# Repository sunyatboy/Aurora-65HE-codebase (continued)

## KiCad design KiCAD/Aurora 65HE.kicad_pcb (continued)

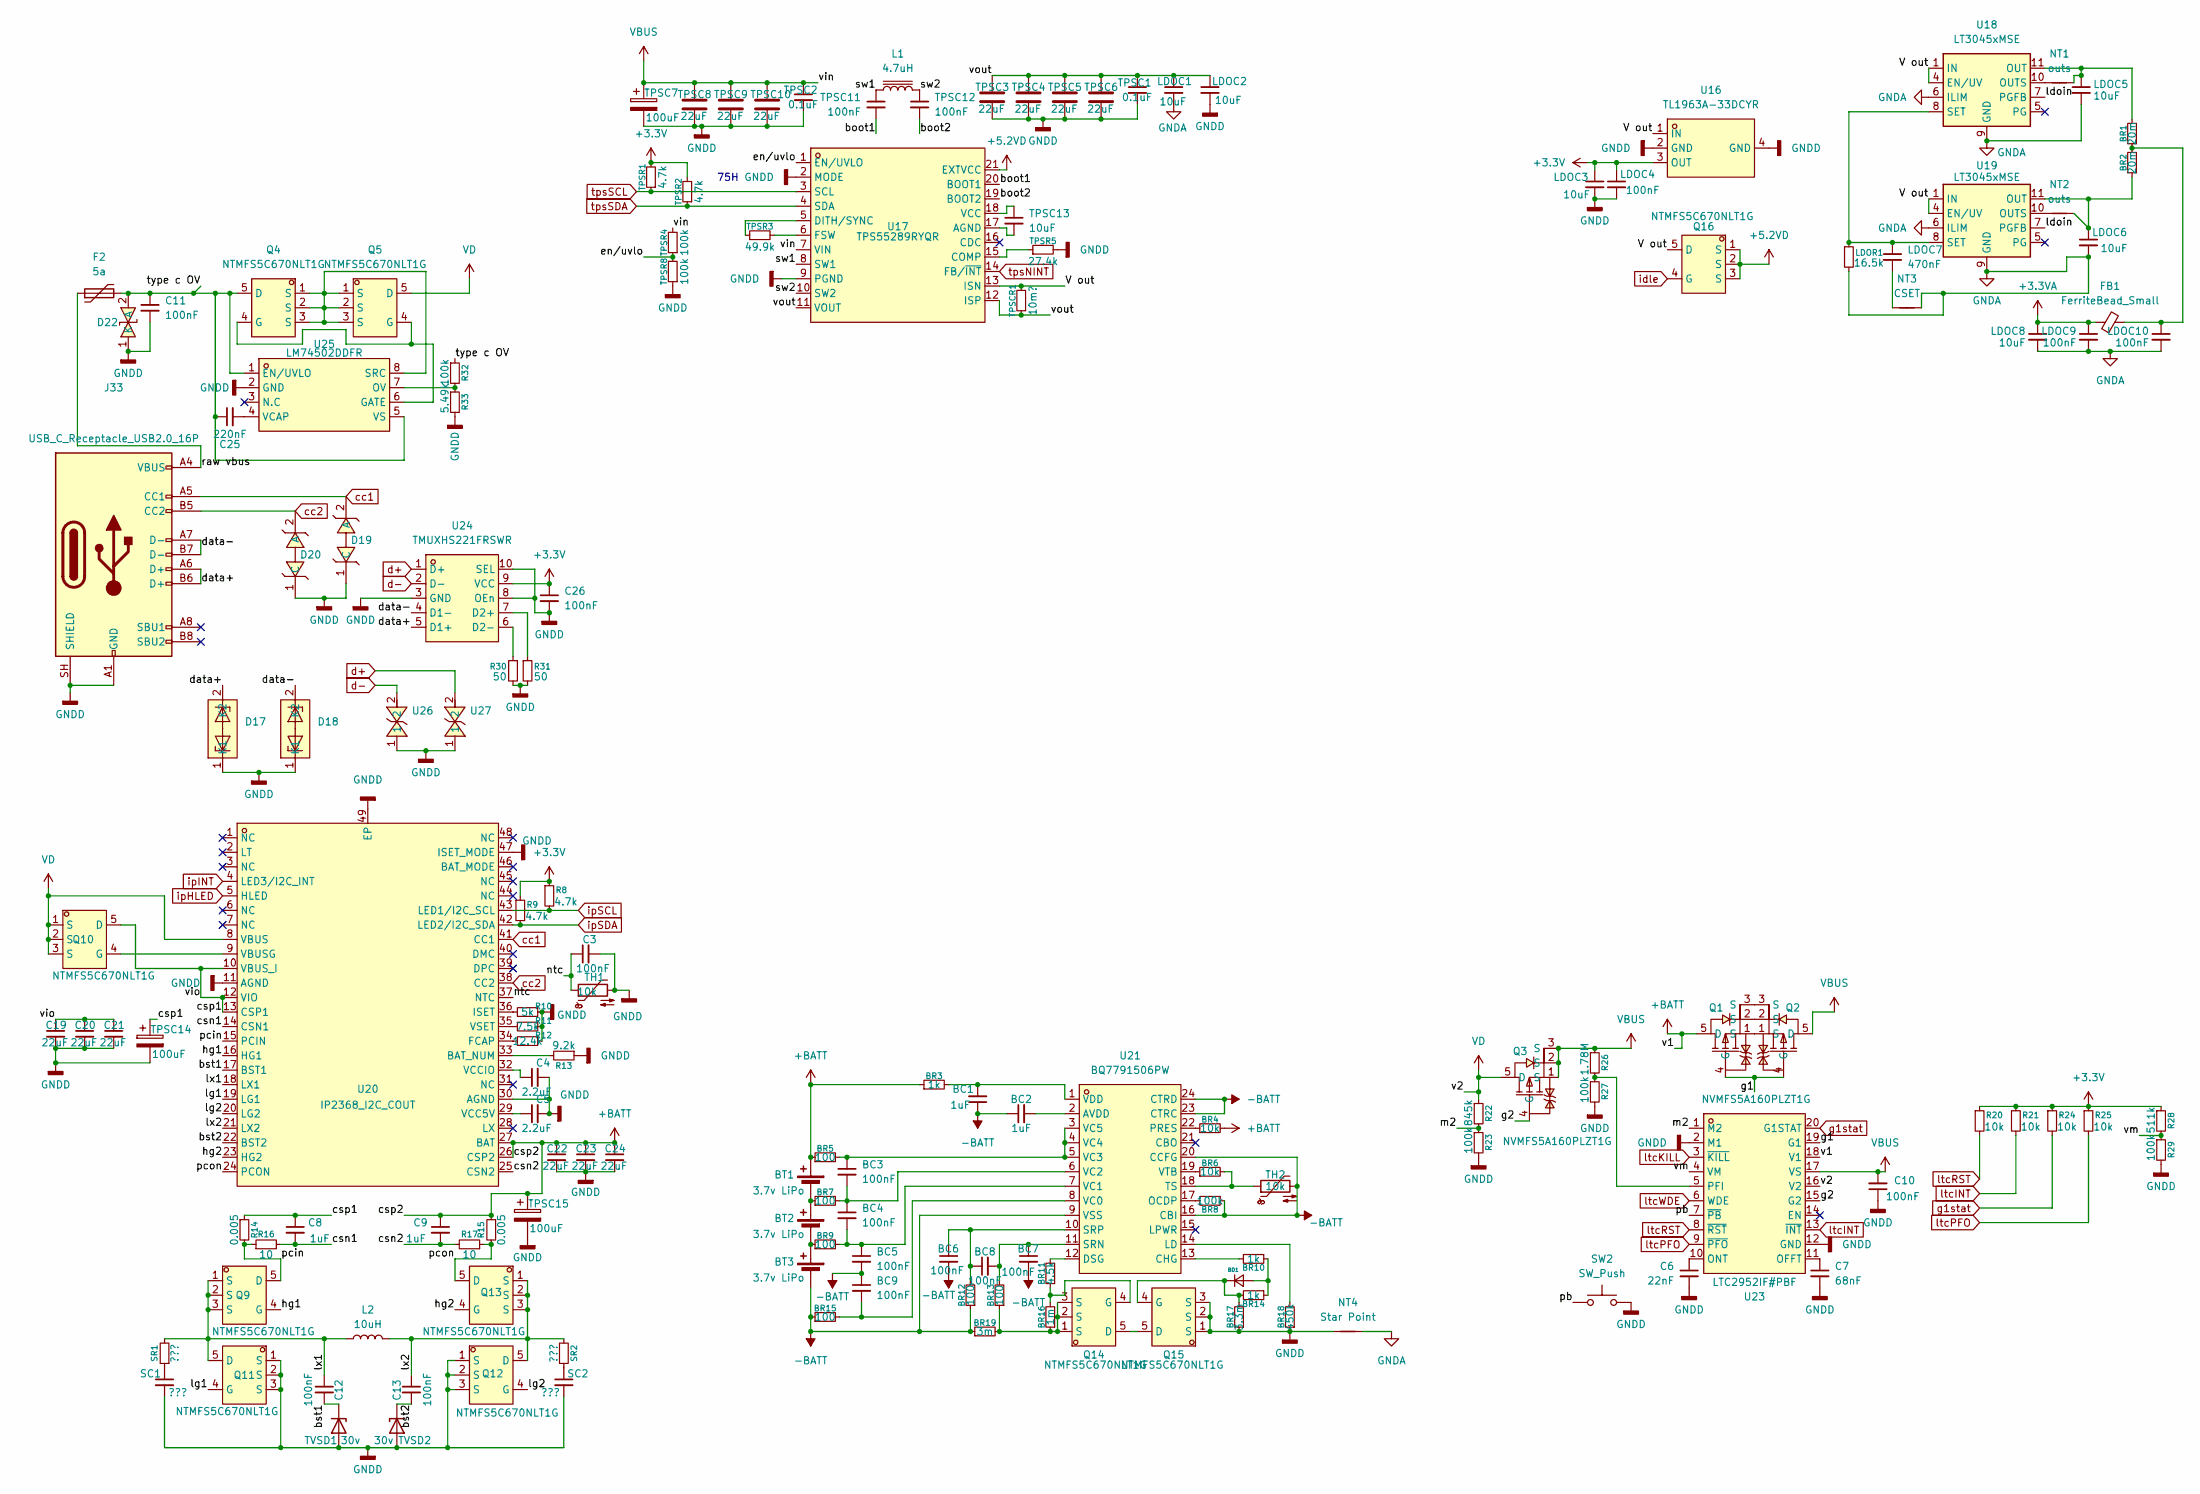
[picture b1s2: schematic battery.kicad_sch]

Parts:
BC1, BC2: 1uF; C_0603_1608Metric
BC3, BC4, BC5, BC6, BC7, BC8, BC9: 100nF; C_0603_1608Metric
BD1: D_0603_1608Metric
BR1, BR2: 20m; R_1206_3216Metric
BR3, BR10, BR14: 1k; R_0603_1608Metric
BR4, BR6: 10k; R_0603_1608Metric
BR5, BR7, BR9, BR12, BR13, BR15: 100; R_0603_1608Metric
BR8: 100k; R_0603_1608Metric
BR11: 4.5k; R_0603_1608Metric
BR16: 1m; R_0603_1608Metric
BR17: 3.3m; R_0603_1608Metric
BR18: 450k; R_0603_1608Metric
BR19: 3m; R_2512_6332Metric
BT1, BT2, BT3: 3.7v LiPo; Battery
C3, C10, C11, C12, C13, C26: 100nF; C_0603_1608Metric
C4, C5: 2.2uF; C_0603_1608Metric
C6: 22nF; C_0603_1608Metric
C7: 68nF; C_0603_1608Metric
C8, C9: 1uF; C_0603_1608Metric
C19, C20, C21, C22, C23, C24: 22uF; C_0603_1608Metric
C25: 220nF; C_0603_1608Metric
D17, D18: PESD24VF1BLYL; DFN1006-2L_L1.0-W0.6-P0.60-BI; MPN PESD24VF1BLYL; LCSC Part C2443373
D19, D20: PESD24VL1BA,115; SOD-323_L1.8-W1.3-LS2.5-BI; MPN PESD24VL1BA,115; LCSC Part C69324
D22: SMBJ24CA_C83268; SMB_L4.6-W3.6-LS5.3-BI; MPN SMBJ24CA; LCSC Part C83268
F2: 5a
FB1: FerriteBead_Small; L_1206_3216Metric
J33: USB_C_Receptacle_USB2.0_16P; USB_C_Receptacle_GCT_USB4105-xx-A_16P_TopMnt_Horizontal
L1: 4.7uH; L_Coilcraft_XAL7070-XXX
L2: 10uH
LDOC1, LDOC2, LDOC3, LDOC5, LDOC6, LDOC8: 10uF; C_1210_3225Metric
LDOC4, LDOC9, LDOC10: 100nF; C_0603_1608Metric
LDOC7: 470nF; C_0603_1608Metric
LDOR1: 16.5k; C_0603_1608Metric
NT1, NT2: outs; NetTie-2_SMD_Pad0.2mm
NT3: CSET; NetTie-2_SMD_Pad0.2mm
NT4: Star Point
Q1, Q2, Q3: NVMFS5A160PLZT1G; DFN-5_L4.9-W5.9-P1.27-LS6.2-BL; MPN NVMFS5A160PLZT1G; LCSC Part C604586
Q4, Q5, Q9, Q10, Q11, Q12, Q13, Q14, Q15, Q16: NTMFS5C670NLT1G; DFN-5_L6.1-W5.1-P1.27-BL; MPN NTMFS5C670NLT1G; LCSC Part C179626
R8, R9: 4.7k; R_0603_1608Metric
R10: 5k; R_0603_1608Metric
R11: 7.5k; R_0603_1608Metric
R12: 12.4k; R_0603_1608Metric
R13: 9.2k; R_0603_1608Metric
R14, R15: 0.005; R_0603_1608Metric
R16, R17: 10; R_0603_1608Metric
R20, R21, R24, R25: 10k; R_0603_1608Metric
R22: 845k; R_0603_1608Metric
R23, R27, R29, R32: 100k; R_0603_1608Metric
R26: 1.78M; R_0603_1608Metric
R28: 511k; R_0603_1608Metric
R30, R31: 50; R_0603_1608Metric
R33: 5.49k; R_0603_1608Metric
SC1, SC2: ???; C_0603_1608Metric
SR1, SR2: ???; R_0603_1608Metric
SW2: SW_Push
TH1, TH2: 10k
TPSC1, TPSC2: 0.1uF; C_0603_1608Metric
TPSC3, TPSC4, TPSC5, TPSC6, TPSC8, TPSC9, TPSC10: 22uF; C_1210_3225Metric
TPSC7, TPSC14, TPSC15: 100uF; C_1210_3225Metric
TPSC11, TPSC12: 100nF; C_0603_1608Metric
TPSC13: 10uF; C_1210_3225Metric
TPSCR1: 10m?; R_2512_6332Metric
TPSR1, TPSR2: 4.7k; C_0603_1608Metric
TPSR3: 49.9k; C_0603_1608Metric
TPSR4, TPSR8: 100k; C_0603_1608Metric
TPSR5: 27.4k; C_0603_1608Metric
TVSD1, TVSD2: 30v
U16: TL1963A-33DCYR; SOT-223_L6.5-W3.5-P2.30-LS7.0-BR; MPN TL1963A-33DCYR; LCSC Part C181262
U17: TPS55289RYQR; VQFN-21_L5.0-W3.0-P0.50-TL; MPN TPS55289RYQR; LCSC Part C5942077
U18, U19: LT3045xMSE; MSOP-12-1EP_3x4.039mm_P0.65mm_EP1.651x2.845mm
U20: IP2368_I2C_COUT; QFN-48_L7.0-W7.0-P0.50-TL-EP5.4-1; MPN IP2368_I2C_COUT; LCSC Part C5372184
U21: BQ7791506PW; TSSOP-24_L7.8-W4.4-P0.65-LS6.4-BR; MPN BQ7791506PW; LCSC Part C2905736
U23: LTC2952IF#PBF; TSSOP-20_L6.5-W4.4-P0.65-LS6.4-BL; MPN LTC2952IF#PBF; LCSC Part C683767
U24: TMUXHS221FRSWR; UQFN-10_L1.8-W1.4-P0.40-TL; MPN TMUXHS221FRSWR; LCSC Part C52989536
U25: LM74502DDFR; SOT-23-8_L2.9-W1.6-P0.65-LS2.8-BL; MPN LM74502DDFR; LCSC Part C3236215
U26, U27: ESD0501BL_C5334572; DFN1006-2L-BI; MPN ESD0501BL; LCSC Part C5334572

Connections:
+3.3V: C26.1, LDOC3.1, LDOC4.1, R8.1, R9.1, R20.1, R21.1, R24.1, R25.1, R28.1, TPSR1.2, TPSR2.2, U16.3 (OUT), U24.9 (VCC); also elsewhere on the board
+3.3VA: FB1.1, LDOC8.1, LDOC9.1; also elsewhere on the board
+5.2VD: Q16.1 (S), Q16.2 (S), Q16.3 (S), U17.21 (EXTVCC); also elsewhere on the board
+BATT: BR3.1, BR4.2, BR5.1, BT1.1 (+), C9.1, C22.1, C23.1, C24.1, Q1.5 (D), R15.1, TPSC15.1, U20.26 (CSP2), U20.27 (BAT), U23.18 (V1)
-BATT: BC1.1, BC2.1, BC5.2, BC6.2, BC7.2, BC9.1, BR8.1, BR12.1, BR15.1, BR19.1, BT3.2 (-), TH2.2, U21.9 (VSS), U21.16 (CBI), U21.20 (CCFG), U21.23 (CTRC), U21.24 (CTRD)
/battery/V out: Q16.5 (D), TPSCR1.2, U16.1 (IN), U17.13 (ISN), U18.1 (IN), U18.2 (IN), U18.3 (IN), U18.4 (EN/UV), U19.1 (IN), U19.2 (IN), U19.3 (IN), U19.4 (EN/UV)
/battery/boot1: TPSC11.2, U17.20 (BOOT1)
/battery/boot2: TPSC12.2, U17.19 (BOOT2)
/battery/bst1: C12.2, TVSD1.1 (K), U20.17 (BST1)
/battery/bst2: C13.2, TVSD2.1 (K), U20.22 (BST2)
/battery/csn1: C8.2, R16.2, U20.14 (CSN1)
/battery/csn2: C9.2, R17.2, U20.25 (CSN2)
/battery/csp1: C8.1, C19.1, C20.1, C21.1, Q10.5 (D), R14.1, TPSC14.1, U20.10 (VBUS_I), U20.12 (VIO), U20.13 (CSP1)
/battery/data+: D17.2 (K2), J33.A6 (D+), J33.B6 (D+), U24.5 (D1+)
/battery/data-: D18.2 (K2), J33.A7 (D-), J33.B7 (D-), U24.4 (D1-)
/battery/en/uvlo: TPSR4.1, TPSR8.2, U17.1 (EN/UVLO)
/battery/g1: Q1.4 (G), Q2.4 (G), U23.19 (G1)
/battery/g2: Q3.4 (G), U23.15 (G2)
/battery/hg1: Q9.4 (G), U20.16 (HG1)
/battery/hg2: Q13.4 (G), U20.23 (HG2)
/battery/ldoin: U18.7 (PGFB), U19.7 (PGFB)
/battery/lg1: Q11.4 (G), U20.19 (LG1)
/battery/lg2: Q12.4 (G), U20.20 (LG2)
/battery/lx1: C12.1, L2.1, Q9.1 (S), Q9.2 (S), Q9.3 (S), Q11.5 (D), SR1.2, U20.18 (LX1)
/battery/lx2: C13.1, L2.2, Q12.5 (D), Q13.1 (S), Q13.2 (S), Q13.3 (S), SR2.2, U20.21 (LX2)
/battery/m2: R22.2, R23.1, U23.1 (M2)
/battery/ntc: C3.1, TH1.1, U20.37 (NTC)
/battery/pb: SW2.1, U23.7 (~PB)
/battery/pcin: Q9.5 (D), R14.2, R16.1, U20.15 (PCIN)
/battery/pcon: Q13.5 (D), R15.2, R17.1, U20.24 (PCON)
/battery/raw vbus: F2.1, J33.A4 (VBUS), J33.A9 (VBUS), J33.B4 (VBUS), J33.B9 (VBUS)
/battery/sw1: L1.1, TPSC11.1, U17.8 (SW1)
/battery/sw2: L1.2, TPSC12.1, U17.10 (SW2)
/battery/type c OV: C11.1, C25.1, D22.2 (A), F2.2, Q4.5 (D), R32.1, U25.1 (EN/UVLO), U25.5 (VS)
/battery/vm: R28.2, R29.1, U23.4 (VM)
/battery/vout: LDOC1.1, LDOC2.1, TPSC1.1, TPSC3.1, TPSC4.1, TPSC5.1, TPSC6.1, TPSCR1.1, U17.11 (VOUT), U17.12 (ISP)
GNDA: LDOC1.2, LDOC5.2, LDOC6.2, LDOC8.2, LDOC9.2, LDOC10.2, LDOR1.2, NT3.2, NT4.2, U18.6 (ILIM), U18.9 (GND), U18.13 (GND), U19.6 (ILIM), U19.9 (GND), U19.13 (GND); also elsewhere on the board
GNDD: BR17.1, BR18.1, C3.2, C4.2, C5.2, C6.2, C7.2, C10.1, C11.2, C19.2, C20.2, C21.2, C22.2, C23.2, C24.2, C26.2, D17.1 (K1), D18.1 (K1), D19.1 (C), D20.1 (C), D22.1 (K), J33.A1 (GND), J33.A12 (GND), J33.B1 (GND), J33.B12 (GND), J33.SH (SHIELD), LDOC2.2, LDOC3.2, LDOC4.2, NT4.1, Q11.1 (S), Q11.2 (S), Q11.3 (S), Q12.1 (S), Q12.2 (S), Q12.3 (S), Q15.1 (S), Q15.2 (S), Q15.3 (S), R10.1, R11.1, R12.1, R13.1, R23.2, R27.2, R29.2, R30.2, R31.2, R33.2, SC1.2, SC2.2, SW2.2, TH1.2, TPSC1.2, TPSC2.2, TPSC3.2, TPSC4.2, TPSC5.2, TPSC6.2, TPSC7.2, TPSC8.2, TPSC9.2, TPSC10.2, TPSC14.2, TPSC15.2, TPSR5.2, TPSR8.1, TVSD1.2 (A), TVSD2.2 (A), U16.2 (GND), U16.4 (GND), U17.2 (MODE), U17.9 (PGND), U20.11 (AGND), U20.30 (AGND), U20.47 (ISET_MODE), U20.49 (EP), U23.2 (M1), U23.12 (GND), U24.3 (GND)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; also elsewhere on the board
unnamed: BD1.2 (A), BR10.1, BR14.1
unnamed: BD1.1 (K), BR14.2, BR17.2, Q15.4 (G)
unnamed: BR1.1, BR2.2, FB1.2, LDOC10.1
unnamed: BR1.2, LDOC5.1, NT1.2, U18.11 (OUT), U18.12 (OUT)
unnamed: BR2.1, LDOC6.1, NT2.2, U19.11 (OUT), U19.12 (OUT)
unnamed: BR13.1, BR16.1, BR19.2, Q14.1 (S), Q14.2 (S), Q14.3 (S)
unnamed: BR7.1, BT1.2 (-), BT2.1 (+)
unnamed: BR9.1, BT2.2 (-), BT3.1 (+)
unnamed: LDOC7.2, NT3.1
unnamed: Q1.1 (S), Q2.1 (S)
unnamed: Q1.2 (S), Q2.2 (S)
unnamed: Q1.3 (S), Q2.3 (S)
unnamed: Q4.4 (G), Q5.4 (G), U25.6 (GATE)
unnamed: Q10.4 (G), U20.9 (VBUSG)
unnamed: Q14.5 (D), Q15.5 (D)
unnamed: BR11.1, BR16.2, Q14.4 (G)
unnamed: SC1.1, SR1.1
unnamed: SC2.1, SR2.1
unnamed: TPSC13.2, U17.17 (AGND)
unnamed: TPSR5.1, U17.15 (COMP)
unnamed: TPSR3.1, U17.5 (DITH/SYNC)
unnamed: TPSR3.2, U17.6 (FSW)
unnamed: TPSC13.1, U17.18 (VCC)
unnamed: NT1.1, U18.10 (OUTS)
unnamed: LDOC7.1, LDOR1.1, U18.8 (SET), U19.8 (SET)
unnamed: NT2.1, U19.10 (OUTS)
unnamed: R13.2, U20.33 (BAT_NUM)
unnamed: R12.2, U20.34 (FCAP)
unnamed: R10.2, U20.36 (ISET)
unnamed: C5.1, U20.29 (VCC5V)
unnamed: C4.1, U20.32 (VCCIO)
unnamed: R11.2, U20.35 (VSET)
unnamed: BC2.2, U21.2 (AVDD)
unnamed: BR10.2, U21.13 (CHG)
unnamed: BR11.2, U21.12 (DSG)
unnamed: BR18.2, U21.14 (LD)
unnamed: BR8.2, U21.17 (OCDP)
unnamed: BR4.1, U21.22 (PRES)
unnamed: BC7.1, BC8.2, BR13.2, U21.11 (SRN)
unnamed: BC6.1, BC8.1, BR12.2, U21.10 (SRP)
unnamed: BR6.2, TH2.1, U21.18 (TS)
unnamed: BC9.2, BR15.2, U21.8 (VC0)
unnamed: BC4.2, BC5.1, BR9.2, U21.7 (VC1)
unnamed: BC3.2, BC4.1, BR7.2, U21.6 (VC2)
unnamed: BC3.1, BR5.2, U21.3 (VC5), U21.4 (VC4), U21.5 (VC3)
unnamed: BC1.2, BR3.2, U21.1 (VDD)
unnamed: BR6.1, U21.19 (VTB)
unnamed: C7.1, U23.11 (OFFT)
unnamed: C6.1, U23.10 (ONT)
unnamed: R26.2, R27.1, U23.5 (PFI)
unnamed: R31.1, U24.7 (D2+)
unnamed: R30.1, U24.6 (D2-)
unnamed: R32.2, R33.1, U25.7 (OV)
unnamed: Q4.1 (S), Q4.2 (S), Q4.3 (S), Q5.1 (S), Q5.2 (S), Q5.3 (S), U25.8 (SRC)
unnamed: C25.2, U25.4 (VCAP)
VBUS: C10.2, Q2.5 (D), Q3.1 (S), Q3.2 (S), Q3.3 (S), R26.1, TPSC2.1, TPSC7.1, TPSC8.1, TPSC9.1, TPSC10.1, TPSR4.2, U17.7 (VIN), U23.17 (VS)
VD: Q3.5 (D), Q5.5 (D), Q10.1 (S), Q10.2 (S), Q10.3 (S), R22.1, U20.8 (VBUS), U23.16 (V2)
cc1: D19.2 (A), J33.A5 (CC1), U20.41 (CC1)
cc2: D20.2 (A), J33.B5 (CC2), U20.38 (CC2)
d+: U24.1 (D+), U27.2; also elsewhere on the board
d-: U24.2 (D-), U26.2; also elsewhere on the board
g1stat: R24.2, U23.20 (G1STAT)
idle: Q16.4 (G)
ipHLED: U20.5 (HLED)
ipINT: U20.4 (LED3/I2C_INT)
ipSCL: R8.2, U20.43 (LED1/I2C_SCL)
ipSDA: R9.2, U20.42 (LED2/I2C_SDA)
ltcINT: R21.2, U23.13 (~INT)
ltcKILL: U23.3 (~KILL)
ltcPFO: R25.2, U23.9 (~PFO)
ltcRST: R20.2, U23.8 (~RST)
ltcWDE: U23.6 (WDE)
tpsNINT: U17.14 (FB/~INT)
tpsSCL: TPSR1.1, U17.3 (SCL)
tpsSDA: TPSR2.1, U17.4 (SDA)

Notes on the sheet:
75H

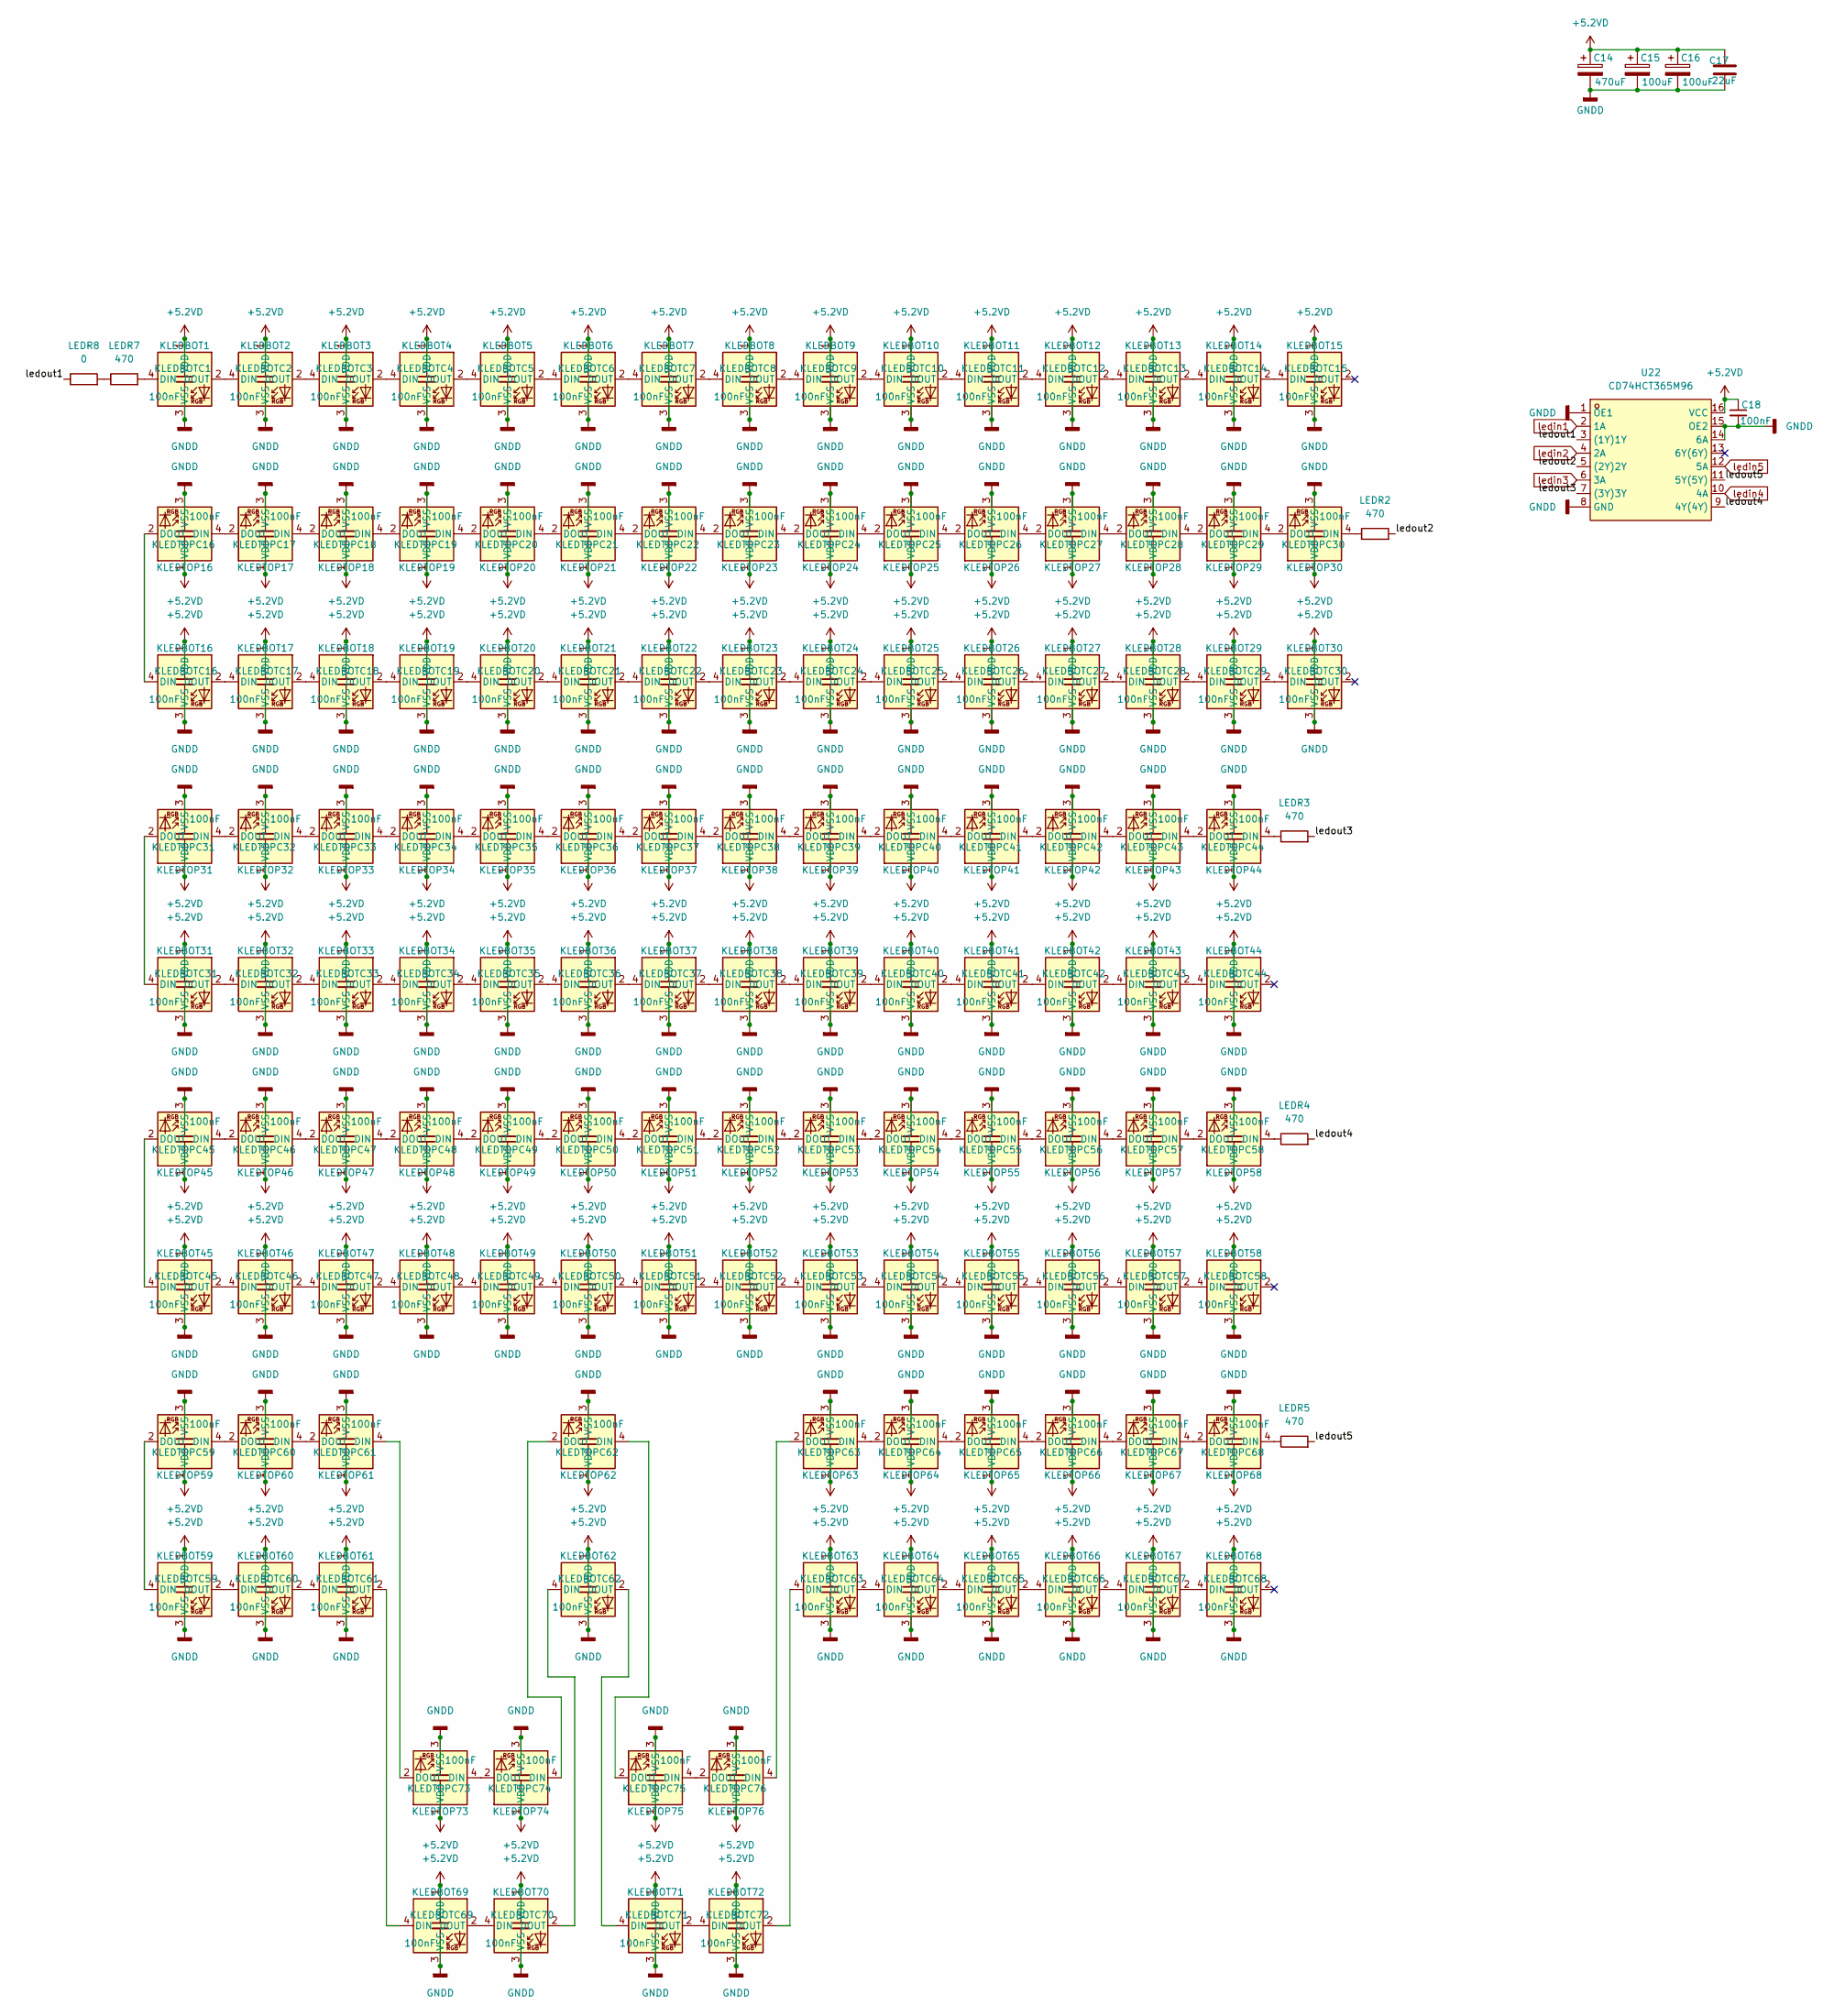
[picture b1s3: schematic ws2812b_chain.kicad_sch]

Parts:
C14: 470uF; C_0603_1608Metric
C15: 100uF; R_1206_3216Metric
C16: 100uF; C_0603_1608Metric
C17: 22uF; C_1210_3225Metric
C18: 100nF; C_0603_1608Metric
KLEDBOT1, KLEDBOT2, KLEDBOT3, KLEDBOT4, KLEDBOT5, KLEDBOT6, KLEDBOT7, KLEDBOT8, KLEDBOT9, KLEDBOT10, KLEDBOT11, KLEDBOT12, KLEDBOT13, KLEDBOT14, KLEDBOT15, KLEDBOT16, KLEDBOT17, KLEDBOT18, KLEDBOT19, KLEDBOT20, KLEDBOT21, KLEDBOT22, KLEDBOT23, KLEDBOT24, KLEDBOT25, KLEDBOT26, KLEDBOT27, KLEDBOT28, KLEDBOT29, KLEDBOT30, KLEDBOT31, KLEDBOT32, KLEDBOT33, KLEDBOT34, KLEDBOT35, KLEDBOT36, KLEDBOT37, KLEDBOT38, KLEDBOT39, KLEDBOT40, KLEDBOT41, KLEDBOT42, KLEDBOT43, KLEDBOT44, KLEDBOT45, KLEDBOT46, KLEDBOT47, KLEDBOT48, KLEDBOT49, KLEDBOT50, KLEDBOT51, KLEDBOT52, KLEDBOT53, KLEDBOT54, KLEDBOT55, KLEDBOT56, KLEDBOT57, KLEDBOT58, KLEDBOT59, KLEDBOT60, KLEDBOT61, KLEDBOT62, KLEDBOT63, KLEDBOT64, KLEDBOT65, KLEDBOT66, KLEDBOT67, KLEDBOT68, KLEDBOT69, KLEDBOT70, KLEDBOT71, KLEDBOT72: WS2812B; LED_WS2812B_PLCC4_5.0x5.0mm_P3.2mm
KLEDBOTC1, KLEDBOTC2, KLEDBOTC3, KLEDBOTC4, KLEDBOTC5, KLEDBOTC6, KLEDBOTC7, KLEDBOTC8, KLEDBOTC9, KLEDBOTC10, KLEDBOTC11, KLEDBOTC12, KLEDBOTC13, KLEDBOTC14, KLEDBOTC15, KLEDBOTC16, KLEDBOTC17, KLEDBOTC18, KLEDBOTC19, KLEDBOTC20, KLEDBOTC21, KLEDBOTC22, KLEDBOTC23, KLEDBOTC24, KLEDBOTC25, KLEDBOTC26, KLEDBOTC27, KLEDBOTC28, KLEDBOTC29, KLEDBOTC30, KLEDBOTC31, KLEDBOTC32, KLEDBOTC33, KLEDBOTC34, KLEDBOTC35, KLEDBOTC36, KLEDBOTC37, KLEDBOTC38, KLEDBOTC39, KLEDBOTC40, KLEDBOTC41, KLEDBOTC42, KLEDBOTC43, KLEDBOTC44, KLEDBOTC45, KLEDBOTC46, KLEDBOTC47, KLEDBOTC48, KLEDBOTC49, KLEDBOTC50, KLEDBOTC51, KLEDBOTC52, KLEDBOTC53, KLEDBOTC54, KLEDBOTC55, KLEDBOTC56, KLEDBOTC57, KLEDBOTC58, KLEDBOTC59, KLEDBOTC60, KLEDBOTC61, KLEDBOTC62, KLEDBOTC63, KLEDBOTC64, KLEDBOTC65, KLEDBOTC66, KLEDBOTC67, KLEDBOTC68, KLEDBOTC69, KLEDBOTC70, KLEDBOTC71, KLEDBOTC72: 100nF; C_0603_1608Metric
KLEDTOP16, KLEDTOP17, KLEDTOP18, KLEDTOP19, KLEDTOP20, KLEDTOP21, KLEDTOP22, KLEDTOP23, KLEDTOP24, KLEDTOP25, KLEDTOP26, KLEDTOP27, KLEDTOP28, KLEDTOP29, KLEDTOP30, KLEDTOP31, KLEDTOP32, KLEDTOP33, KLEDTOP34, KLEDTOP35, KLEDTOP36, KLEDTOP37, KLEDTOP38, KLEDTOP39, KLEDTOP40, KLEDTOP41, KLEDTOP42, KLEDTOP43, KLEDTOP44, KLEDTOP45, KLEDTOP46, KLEDTOP47, KLEDTOP48, KLEDTOP49, KLEDTOP50, KLEDTOP51, KLEDTOP52, KLEDTOP53, KLEDTOP54, KLEDTOP55, KLEDTOP56, KLEDTOP57, KLEDTOP58, KLEDTOP59, KLEDTOP60, KLEDTOP61, KLEDTOP62, KLEDTOP63, KLEDTOP64, KLEDTOP65, KLEDTOP66, KLEDTOP67, KLEDTOP68, KLEDTOP73, KLEDTOP74, KLEDTOP75, KLEDTOP76: WS2812B; LED_WS2812B_PLCC4_5.0x5.0mm_P3.2mm
KLEDTOPC16, KLEDTOPC17, KLEDTOPC18, KLEDTOPC19, KLEDTOPC20, KLEDTOPC21, KLEDTOPC22, KLEDTOPC23, KLEDTOPC24, KLEDTOPC25, KLEDTOPC26, KLEDTOPC27, KLEDTOPC28, KLEDTOPC29, KLEDTOPC30, KLEDTOPC31, KLEDTOPC32, KLEDTOPC33, KLEDTOPC34, KLEDTOPC35, KLEDTOPC36, KLEDTOPC37, KLEDTOPC38, KLEDTOPC39, KLEDTOPC40, KLEDTOPC41, KLEDTOPC42, KLEDTOPC43, KLEDTOPC44, KLEDTOPC45, KLEDTOPC46, KLEDTOPC47, KLEDTOPC48, KLEDTOPC49, KLEDTOPC50, KLEDTOPC51, KLEDTOPC52, KLEDTOPC53, KLEDTOPC54, KLEDTOPC55, KLEDTOPC56, KLEDTOPC57, KLEDTOPC58, KLEDTOPC59, KLEDTOPC60, KLEDTOPC61, KLEDTOPC62, KLEDTOPC63, KLEDTOPC64, KLEDTOPC65, KLEDTOPC66, KLEDTOPC67, KLEDTOPC68, KLEDTOPC73, KLEDTOPC74, KLEDTOPC75, KLEDTOPC76: 100nF; C_0603_1608Metric
LEDR2, LEDR3, LEDR4, LEDR5: 470; LED_2512_6332Metric
LEDR7: 470; C_0603_1608Metric
LEDR8: 0; LED_2512_6332Metric
U22: CD74HCT365M96; SOIC-16_L9.9-W3.9-P1.27-LS6.0-BL-1; MPN CD74HCT365M96; LCSC Part C2676054

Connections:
+5.2VD: C14.1, C15.1, C16.1, C17.1, C18.1, KLEDBOT1.1 (VDD), KLEDBOT2.1 (VDD), KLEDBOT3.1 (VDD), KLEDBOT4.1 (VDD), KLEDBOT5.1 (VDD), KLEDBOT6.1 (VDD), KLEDBOT7.1 (VDD), KLEDBOT8.1 (VDD), KLEDBOT9.1 (VDD), KLEDBOT10.1 (VDD), KLEDBOT11.1 (VDD), KLEDBOT12.1 (VDD), KLEDBOT13.1 (VDD), KLEDBOT14.1 (VDD), KLEDBOT15.1 (VDD), KLEDBOT16.1 (VDD), KLEDBOT17.1 (VDD), KLEDBOT18.1 (VDD), KLEDBOT19.1 (VDD), KLEDBOT20.1 (VDD), KLEDBOT21.1 (VDD), KLEDBOT22.1 (VDD), KLEDBOT23.1 (VDD), KLEDBOT24.1 (VDD), KLEDBOT25.1 (VDD), KLEDBOT26.1 (VDD), KLEDBOT27.1 (VDD), KLEDBOT28.1 (VDD), KLEDBOT29.1 (VDD), KLEDBOT30.1 (VDD), KLEDBOT31.1 (VDD), KLEDBOT32.1 (VDD), KLEDBOT33.1 (VDD), KLEDBOT34.1 (VDD), KLEDBOT35.1 (VDD), KLEDBOT36.1 (VDD), KLEDBOT37.1 (VDD), KLEDBOT38.1 (VDD), KLEDBOT39.1 (VDD), KLEDBOT40.1 (VDD), KLEDBOT41.1 (VDD), KLEDBOT42.1 (VDD), KLEDBOT43.1 (VDD), KLEDBOT44.1 (VDD), KLEDBOT45.1 (VDD), KLEDBOT46.1 (VDD), KLEDBOT47.1 (VDD), KLEDBOT48.1 (VDD), KLEDBOT49.1 (VDD), KLEDBOT50.1 (VDD), KLEDBOT51.1 (VDD), KLEDBOT52.1 (VDD), KLEDBOT53.1 (VDD), KLEDBOT54.1 (VDD), KLEDBOT55.1 (VDD), KLEDBOT56.1 (VDD), KLEDBOT57.1 (VDD), KLEDBOT58.1 (VDD), KLEDBOT59.1 (VDD), KLEDBOT60.1 (VDD), KLEDBOT61.1 (VDD), KLEDBOT62.1 (VDD), KLEDBOT63.1 (VDD), KLEDBOT64.1 (VDD), KLEDBOT65.1 (VDD), KLEDBOT66.1 (VDD), KLEDBOT67.1 (VDD), KLEDBOT68.1 (VDD), KLEDBOT69.1 (VDD), KLEDBOT70.1 (VDD), KLEDBOT71.1 (VDD), KLEDBOT72.1 (VDD), KLEDBOTC1.1, KLEDBOTC2.1, KLEDBOTC3.1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; also elsewhere on the board
/Gemini Lighting/ledout1: LEDR8.1, U22.3 ((1Y)1Y)
/Gemini Lighting/ledout2: LEDR2.2, U22.5 ((2Y)2Y)
/Gemini Lighting/ledout3: LEDR3.2, U22.7 ((3Y)3Y)
/Gemini Lighting/ledout4: LEDR4.2, U22.9 (4Y(4Y))
/Gemini Lighting/ledout5: LEDR5.2, U22.11 (5Y(5Y))
GNDD: C14.2, C15.2, C16.2, C17.2, C18.2, KLEDBOT1.3 (VSS), KLEDBOT2.3 (VSS), KLEDBOT3.3 (VSS), KLEDBOT4.3 (VSS), KLEDBOT5.3 (VSS), KLEDBOT6.3 (VSS), KLEDBOT7.3 (VSS), KLEDBOT8.3 (VSS), KLEDBOT9.3 (VSS), KLEDBOT10.3 (VSS), KLEDBOT11.3 (VSS), KLEDBOT12.3 (VSS), KLEDBOT13.3 (VSS), KLEDBOT14.3 (VSS), KLEDBOT15.3 (VSS), KLEDBOT16.3 (VSS), KLEDBOT17.3 (VSS), KLEDBOT18.3 (VSS), KLEDBOT19.3 (VSS), KLEDBOT20.3 (VSS), KLEDBOT21.3 (VSS), KLEDBOT22.3 (VSS), KLEDBOT23.3 (VSS), KLEDBOT24.3 (VSS), KLEDBOT25.3 (VSS), KLEDBOT26.3 (VSS), KLEDBOT27.3 (VSS), KLEDBOT28.3 (VSS), KLEDBOT29.3 (VSS), KLEDBOT30.3 (VSS), KLEDBOT31.3 (VSS), KLEDBOT32.3 (VSS), KLEDBOT33.3 (VSS), KLEDBOT34.3 (VSS), KLEDBOT35.3 (VSS), KLEDBOT36.3 (VSS), KLEDBOT37.3 (VSS), KLEDBOT38.3 (VSS), KLEDBOT39.3 (VSS), KLEDBOT40.3 (VSS), KLEDBOT41.3 (VSS), KLEDBOT42.3 (VSS), KLEDBOT43.3 (VSS), KLEDBOT44.3 (VSS), KLEDBOT45.3 (VSS), KLEDBOT46.3 (VSS), KLEDBOT47.3 (VSS), KLEDBOT48.3 (VSS), KLEDBOT49.3 (VSS), KLEDBOT50.3 (VSS), KLEDBOT51.3 (VSS), KLEDBOT52.3 (VSS), KLEDBOT53.3 (VSS), KLEDBOT54.3 (VSS), KLEDBOT55.3 (VSS), KLEDBOT56.3 (VSS), KLEDBOT57.3 (VSS), KLEDBOT58.3 (VSS), KLEDBOT59.3 (VSS), KLEDBOT60.3 (VSS), KLEDBOT61.3 (VSS), KLEDBOT62.3 (VSS), KLEDBOT63.3 (VSS), KLEDBOT64.3 (VSS), KLEDBOT65.3 (VSS), KLEDBOT66.3 (VSS), KLEDBOT67.3 (VSS), KLEDBOT68.3 (VSS), KLEDBOT69.3 (VSS), KLEDBOT70.3 (VSS), KLEDBOT71.3 (VSS), KLEDBOT72.3 (VSS), KLEDBOTC1.2, KLEDBOTC2.2, KLEDBOTC3.2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; also elsewhere on the board
unnamed: KLEDBOT1.4 (DIN), LEDR7.2
unnamed: KLEDBOT1.2 (DOUT), KLEDBOT2.4 (DIN)
unnamed: KLEDBOT2.2 (DOUT), KLEDBOT3.4 (DIN)
unnamed: KLEDBOT3.2 (DOUT), KLEDBOT4.4 (DIN)
unnamed: KLEDBOT4.2 (DOUT), KLEDBOT5.4 (DIN)
unnamed: KLEDBOT5.2 (DOUT), KLEDBOT6.4 (DIN)
unnamed: KLEDBOT6.2 (DOUT), KLEDBOT7.4 (DIN)
unnamed: KLEDBOT7.2 (DOUT), KLEDBOT8.4 (DIN)
unnamed: KLEDBOT8.2 (DOUT), KLEDBOT9.4 (DIN)
unnamed: KLEDBOT9.2 (DOUT), KLEDBOT10.4 (DIN)
unnamed: KLEDBOT10.2 (DOUT), KLEDBOT11.4 (DIN)
unnamed: KLEDBOT11.2 (DOUT), KLEDBOT12.4 (DIN)
unnamed: KLEDBOT12.2 (DOUT), KLEDBOT13.4 (DIN)
unnamed: KLEDBOT13.2 (DOUT), KLEDBOT14.4 (DIN)
unnamed: KLEDBOT14.2 (DOUT), KLEDBOT15.4 (DIN)
unnamed: KLEDBOT16.4 (DIN), KLEDTOP16.2 (DOUT)
unnamed: KLEDBOT16.2 (DOUT), KLEDBOT17.4 (DIN)
unnamed: KLEDBOT17.2 (DOUT), KLEDBOT18.4 (DIN)
unnamed: KLEDBOT18.2 (DOUT), KLEDBOT19.4 (DIN)
unnamed: KLEDBOT19.2 (DOUT), KLEDBOT20.4 (DIN)
unnamed: KLEDBOT20.2 (DOUT), KLEDBOT21.4 (DIN)
unnamed: KLEDBOT21.2 (DOUT), KLEDBOT22.4 (DIN)
unnamed: KLEDBOT22.2 (DOUT), KLEDBOT23.4 (DIN)
unnamed: KLEDBOT23.2 (DOUT), KLEDBOT24.4 (DIN)
unnamed: KLEDBOT24.2 (DOUT), KLEDBOT25.4 (DIN)
unnamed: KLEDBOT25.2 (DOUT), KLEDBOT26.4 (DIN)
unnamed: KLEDBOT26.2 (DOUT), KLEDBOT27.4 (DIN)
unnamed: KLEDBOT27.2 (DOUT), KLEDBOT28.4 (DIN)
unnamed: KLEDBOT28.2 (DOUT), KLEDBOT29.4 (DIN)
unnamed: KLEDBOT29.2 (DOUT), KLEDBOT30.4 (DIN)
unnamed: KLEDBOT31.4 (DIN), KLEDTOP31.2 (DOUT)
unnamed: KLEDBOT31.2 (DOUT), KLEDBOT32.4 (DIN)
unnamed: KLEDBOT32.2 (DOUT), KLEDBOT33.4 (DIN)
unnamed: KLEDBOT33.2 (DOUT), KLEDBOT34.4 (DIN)
unnamed: KLEDBOT34.2 (DOUT), KLEDBOT35.4 (DIN)
unnamed: KLEDBOT35.2 (DOUT), KLEDBOT36.4 (DIN)
unnamed: KLEDBOT36.2 (DOUT), KLEDBOT37.4 (DIN)
unnamed: KLEDBOT37.2 (DOUT), KLEDBOT38.4 (DIN)
unnamed: KLEDBOT38.2 (DOUT), KLEDBOT39.4 (DIN)
unnamed: KLEDBOT39.2 (DOUT), KLEDBOT40.4 (DIN)
unnamed: KLEDBOT40.2 (DOUT), KLEDBOT41.4 (DIN)
unnamed: KLEDBOT41.2 (DOUT), KLEDBOT42.4 (DIN)
unnamed: KLEDBOT42.2 (DOUT), KLEDBOT43.4 (DIN)
unnamed: KLEDBOT43.2 (DOUT), KLEDBOT44.4 (DIN)
unnamed: KLEDBOT45.4 (DIN), KLEDTOP45.2 (DOUT)
unnamed: KLEDBOT45.2 (DOUT), KLEDBOT46.4 (DIN)
unnamed: KLEDBOT46.2 (DOUT), KLEDBOT47.4 (DIN)
unnamed: KLEDBOT47.2 (DOUT), KLEDBOT48.4 (DIN)
unnamed: KLEDBOT48.2 (DOUT), KLEDBOT49.4 (DIN)
unnamed: KLEDBOT49.2 (DOUT), KLEDBOT50.4 (DIN)
unnamed: KLEDBOT50.2 (DOUT), KLEDBOT51.4 (DIN)
unnamed: KLEDBOT51.2 (DOUT), KLEDBOT52.4 (DIN)
unnamed: KLEDBOT52.2 (DOUT), KLEDBOT53.4 (DIN)
unnamed: KLEDBOT53.2 (DOUT), KLEDBOT54.4 (DIN)
unnamed: KLEDBOT54.2 (DOUT), KLEDBOT55.4 (DIN)
unnamed: KLEDBOT55.2 (DOUT), KLEDBOT56.4 (DIN)
unnamed: KLEDBOT56.2 (DOUT), KLEDBOT57.4 (DIN)
unnamed: KLEDBOT57.2 (DOUT), KLEDBOT58.4 (DIN)
unnamed: KLEDBOT59.4 (DIN), KLEDTOP59.2 (DOUT)
unnamed: KLEDBOT59.2 (DOUT), KLEDBOT60.4 (DIN)
unnamed: KLEDBOT60.2 (DOUT), KLEDBOT61.4 (DIN)
unnamed: KLEDBOT61.2 (DOUT), KLEDBOT69.4 (DIN)
unnamed: KLEDBOT62.4 (DIN), KLEDBOT70.2 (DOUT)
unnamed: KLEDBOT62.2 (DOUT), KLEDBOT71.4 (DIN)
unnamed: KLEDBOT63.4 (DIN), KLEDBOT72.2 (DOUT)
unnamed: KLEDBOT63.2 (DOUT), KLEDBOT64.4 (DIN)
unnamed: KLEDBOT64.2 (DOUT), KLEDBOT65.4 (DIN)
unnamed: KLEDBOT65.2 (DOUT), KLEDBOT66.4 (DIN)
unnamed: KLEDBOT66.2 (DOUT), KLEDBOT67.4 (DIN)
unnamed: KLEDBOT67.2 (DOUT), KLEDBOT68.4 (DIN)
unnamed: KLEDBOT69.2 (DOUT), KLEDBOT70.4 (DIN)
unnamed: KLEDBOT71.2 (DOUT), KLEDBOT72.4 (DIN)
unnamed: KLEDTOP16.4 (DIN), KLEDTOP17.2 (DOUT)
unnamed: KLEDTOP17.4 (DIN), KLEDTOP18.2 (DOUT)
unnamed: KLEDTOP18.4 (DIN), KLEDTOP19.2 (DOUT)
unnamed: KLEDTOP19.4 (DIN), KLEDTOP20.2 (DOUT)
unnamed: KLEDTOP20.4 (DIN), KLEDTOP21.2 (DOUT)
unnamed: KLEDTOP21.4 (DIN), KLEDTOP22.2 (DOUT)
unnamed: KLEDTOP22.4 (DIN), KLEDTOP23.2 (DOUT)
unnamed: KLEDTOP23.4 (DIN), KLEDTOP24.2 (DOUT)
unnamed: KLEDTOP24.4 (DIN), KLEDTOP25.2 (DOUT)
unnamed: KLEDTOP25.4 (DIN), KLEDTOP26.2 (DOUT)
unnamed: KLEDTOP26.4 (DIN), KLEDTOP27.2 (DOUT)
unnamed: KLEDTOP27.4 (DIN), KLEDTOP28.2 (DOUT)
unnamed: KLEDTOP28.4 (DIN), KLEDTOP29.2 (DOUT)
unnamed: KLEDTOP29.4 (DIN), KLEDTOP30.2 (DOUT)
unnamed: KLEDTOP30.4 (DIN), LEDR2.1
unnamed: KLEDTOP31.4 (DIN), KLEDTOP32.2 (DOUT)
unnamed: KLEDTOP32.4 (DIN), KLEDTOP33.2 (DOUT)
unnamed: KLEDTOP33.4 (DIN), KLEDTOP34.2 (DOUT)
unnamed: KLEDTOP34.4 (DIN), KLEDTOP35.2 (DOUT)
unnamed: KLEDTOP35.4 (DIN), KLEDTOP36.2 (DOUT)
unnamed: KLEDTOP36.4 (DIN), KLEDTOP37.2 (DOUT)
unnamed: KLEDTOP37.4 (DIN), KLEDTOP38.2 (DOUT)
unnamed: KLEDTOP38.4 (DIN), KLEDTOP39.2 (DOUT)
unnamed: KLEDTOP39.4 (DIN), KLEDTOP40.2 (DOUT)
unnamed: KLEDTOP40.4 (DIN), KLEDTOP41.2 (DOUT)
unnamed: KLEDTOP41.4 (DIN), KLEDTOP42.2 (DOUT)
unnamed: KLEDTOP42.4 (DIN), KLEDTOP43.2 (DOUT)
unnamed: KLEDTOP43.4 (DIN), KLEDTOP44.2 (DOUT)
unnamed: KLEDTOP44.4 (DIN), LEDR3.1
unnamed: KLEDTOP45.4 (DIN), KLEDTOP46.2 (DOUT)
unnamed: KLEDTOP46.4 (DIN), KLEDTOP47.2 (DOUT)
unnamed: KLEDTOP47.4 (DIN), KLEDTOP48.2 (DOUT)
unnamed: KLEDTOP48.4 (DIN), KLEDTOP49.2 (DOUT)
unnamed: KLEDTOP49.4 (DIN), KLEDTOP50.2 (DOUT)
unnamed: KLEDTOP50.4 (DIN), KLEDTOP51.2 (DOUT)
unnamed: KLEDTOP51.4 (DIN), KLEDTOP52.2 (DOUT)
unnamed: KLEDTOP52.4 (DIN), KLEDTOP53.2 (DOUT)
unnamed: KLEDTOP53.4 (DIN), KLEDTOP54.2 (DOUT)
unnamed: KLEDTOP54.4 (DIN), KLEDTOP55.2 (DOUT)
unnamed: KLEDTOP55.4 (DIN), KLEDTOP56.2 (DOUT)
unnamed: KLEDTOP56.4 (DIN), KLEDTOP57.2 (DOUT)
unnamed: KLEDTOP57.4 (DIN), KLEDTOP58.2 (DOUT)
unnamed: KLEDTOP58.4 (DIN), LEDR4.1
unnamed: KLEDTOP59.4 (DIN), KLEDTOP60.2 (DOUT)
unnamed: KLEDTOP60.4 (DIN), KLEDTOP61.2 (DOUT)
unnamed: KLEDTOP61.4 (DIN), KLEDTOP73.2 (DOUT)
unnamed: KLEDTOP62.4 (DIN), KLEDTOP75.2 (DOUT)
unnamed: KLEDTOP62.2 (DOUT), KLEDTOP74.4 (DIN)
unnamed: KLEDTOP63.4 (DIN), KLEDTOP64.2 (DOUT)
unnamed: KLEDTOP63.2 (DOUT), KLEDTOP76.4 (DIN)
unnamed: KLEDTOP64.4 (DIN), KLEDTOP65.2 (DOUT)
unnamed: KLEDTOP65.4 (DIN), KLEDTOP66.2 (DOUT)
unnamed: KLEDTOP66.4 (DIN), KLEDTOP67.2 (DOUT)
unnamed: KLEDTOP67.4 (DIN), KLEDTOP68.2 (DOUT)
unnamed: KLEDTOP68.4 (DIN), LEDR5.1
unnamed: KLEDTOP73.4 (DIN), KLEDTOP74.2 (DOUT)
unnamed: KLEDTOP75.4 (DIN), KLEDTOP76.2 (DOUT)
unnamed: LEDR7.1, LEDR8.2
ledin1: U22.2 (1A)
ledin2: U22.4 (2A)
ledin3: U22.6 (3A)
ledin4: U22.10 (4A)
ledin5: U22.12 (5A)
